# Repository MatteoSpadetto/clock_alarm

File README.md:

# alarm_clock
ESP32 clock alarm just for fun with gerber and 3D files

This alarm uses as intrface an IMU so:
1) shaking stop or engange the bell
2) rotation in 3D space change the led matrix RGB colors

With the 3 buttons is possible to set the alarm time.

Time and zone are automatically set via WiFi connection.
7-segment display used to show time and user interface feedbacks.

The box and structure is 3D printed with SLM tech
The matrix led cover was made with a laser cutter on plexiglass

Circuit board PCB was design with KiCad and hand soldered

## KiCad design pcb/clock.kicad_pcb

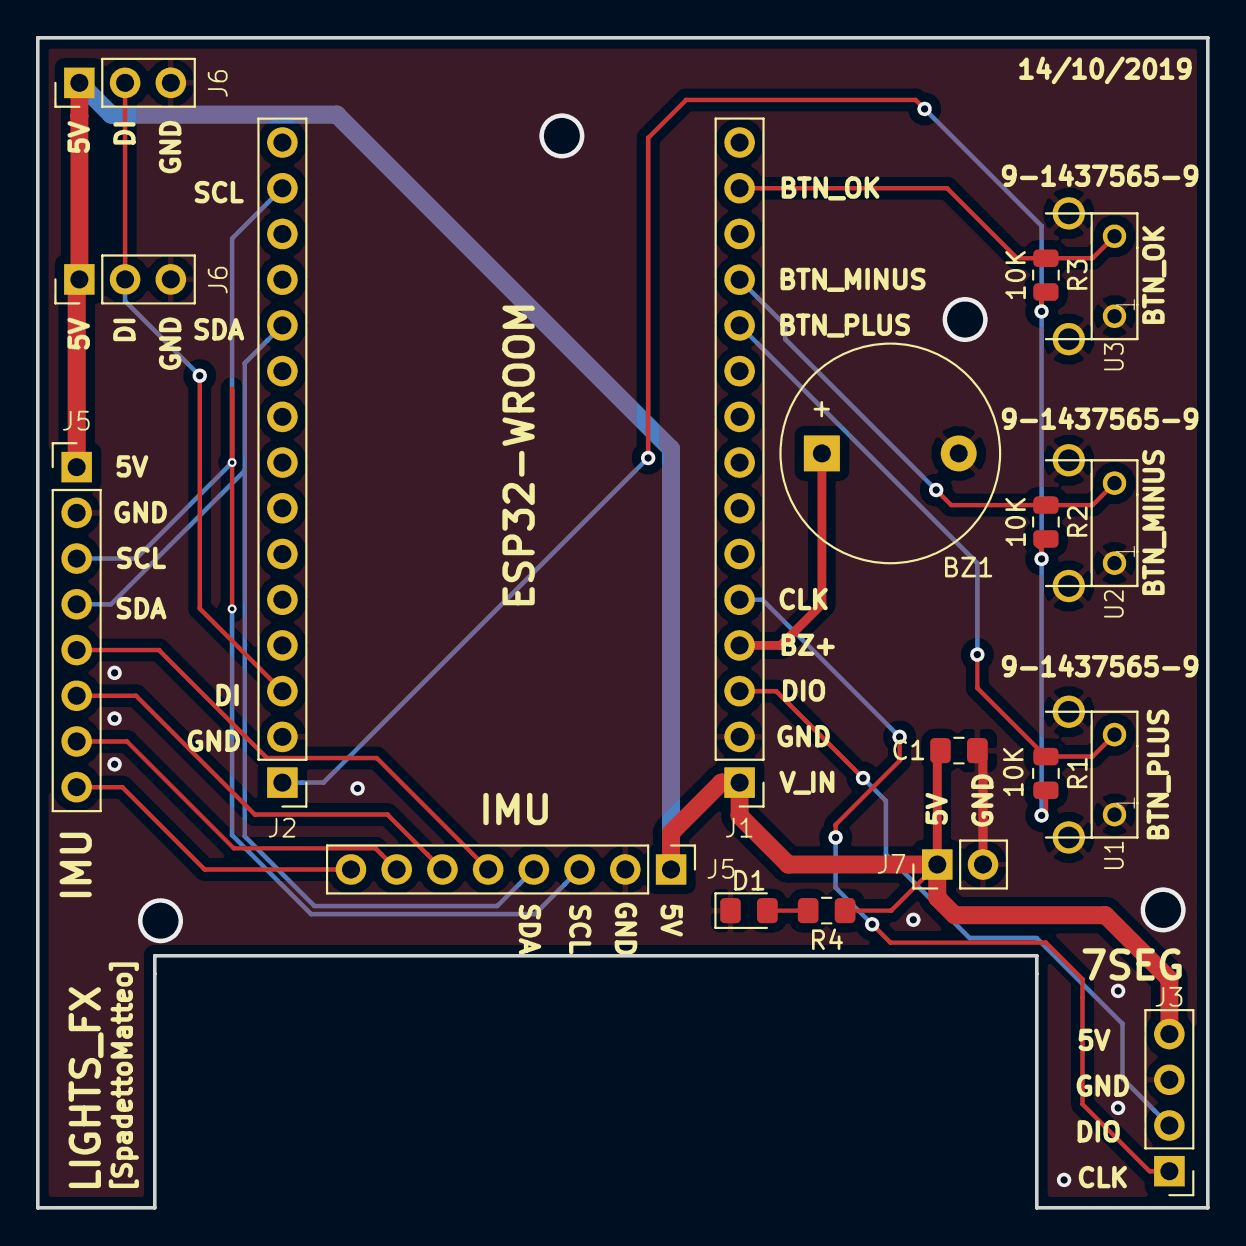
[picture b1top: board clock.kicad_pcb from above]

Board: 2 copper layers, 65.0 x 65.0 mm, 18 parts (0 on the bottom side), 17 nets.

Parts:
BZ1: Buzzer; Buzzer_12x9.5RM7.6
C1: 1uF; C_0805_2012Metric_Pad1.15x1.40mm_HandSolder
D1: LED; LED_0805_2012Metric_Pad1.15x1.40mm_HandSolder
J1, J2: Conn_01x15_Female_ESP32; PinHeader_1x15_P2.54mm_Vertical
J3: Conn_01x04_Female_7seg4d; PinHeader_1x04_P2.54mm_Vertical
J5, J5#2: Conn_01x08_Female_IMU; PinHeader_1x08_P2.54mm_Vertical
J6, J6#2: Conn_01x03_Female_Pixel; PinHeader_1x03_P2.54mm_Vertical
J7: Conn_01x02_Female_PW; PinHeader_1x02_P2.54mm_Vertical
R1, R2, R3: 10K; R_0805_2012Metric
R4: 330; R_0805_2012Metric_Pad1.15x1.40mm_HandSolder
U1, U2, U3: 9-1437565-9; FSMRACD

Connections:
+3V3: J2.1, R1.2, R2.2, R3.2
+5V: C1.1, J1.1, J3.4, J5.1, J5#2.1, J6.1, J6#2.1, J7.1, R4.1
/BTN_MINUS: J1.12, R2.1, U2.P$2
/BTN_OK: J1.11, R1.1, U1.P$2
/BTN_PLUS: J1.14, R3.1, U3.P$2
/BUZZER+: BZ1.1, J1.4
/CLK: J1.5, J3.1
/DI: J2.3, J6.2, J6#2.2
/DIO: J1.3, J3.2
/SCL: J2.14, J5.3, J5#2.3
/SDA: J2.11, J5.4, J5#2.4
GND: BZ1.2, C1.2, D1.1, J1.2, J2.2, J3.3, J5.2, J5#2.2, J6.3, J6#2.3, J7.2, U1.GND1, U1.GND2, U1.P$1, U2.GND1, U2.GND2, U2.P$1, U3.GND1, U3.GND2, U3.P$1
unnamed: D1.2, R4.2
unnamed: J5.5, J5#2.5
unnamed: J5.6, J5#2.6
unnamed: J5.7, J5#2.7
unnamed: J5.8, J5#2.8

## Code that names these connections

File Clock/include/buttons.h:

//                             ___          ___                 ___          ___         ___     //
//                            /\__\        /\  \               /\__\        /\__\      /|  |     //
//                 ___       /:/ _/_       \:\  \       ___   /:/ _/_      /:/ _/_    |:|  |     //
//                /\__\     /:/ /\  \       \:\  \     /\__\ /:/ /\  \    /:/ /\__\   |:|  |     //
//  ___     ___  /:/__/    /:/ /::\  \  ___ /::\  \   /:/  //:/ /::\  \  /:/ /:/  / __|:|__|     //
// /\  \   /\__\/::\  \   /:/__\/\:\__\/\  /:/\:\__\ /:/__//:/_/:/\:\__\/:/_/:/  / /::::\__\_____//
// \:\  \ /:/  /\/\:\  \__\:\  \ /:/  /\:\/:/  \/__//::\  \\:\/:/ /:/  /\:\/:/  /  ~~~~\::::/___///
//  \:\  /:/  /  ~~\:\/\__\\:\  /:/  /  \::/__/    /:/\:\  \\::/ /:/  /  \::/__/       |:|~~|    //
//   \:\/:/  /      \::/  / \:\/:/  /    \:\  \    \/__\:\  \\/_/:/  /    \:\  \       |:|  |    //
//    \::/  /       /:/  /   \::/  /      \:\__\        \:\__\ /:/  /      \:\__\      |:|__|    //
//     \/__/        \/__/     \/__/        \/__/         \/__/ \/__/        \/__/      |/__/     //

#ifndef _BUTTONS_H
#define _BUTTONS_H

#include <Arduino.h>

#define BTN_PLUS 35
#define BTN_MINUS 34
#define BTN_OK 36
#define MAX_HOUR 1439 //In minutes
#define MIN_HOUR 0
#define SET_ALARM_TIMEOUT 5000

struct Button
{
  const uint8_t PIN;
  uint32_t numberKeyPresses;
  bool pressed;
};

Button buttonPlus = {BTN_PLUS, 0, false};
Button buttonMinus = {BTN_MINUS, 0, false};
Button buttonOk = {BTN_OK, 0, false};

int setAlarm = 0;
int setAlarmPeriod;
int alarmTimeSet;

int timeDeboun;
int timeDebounTot;

void onButtonClick();

#endif

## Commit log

2022-06-15 Adding board images
